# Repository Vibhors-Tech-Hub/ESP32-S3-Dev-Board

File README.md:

# ESP32-S3 Development Board

A professional-grade, high-performance **ESP32-S3 Development Board**. This hardware implementation uses a 4-layer PCB stackup to optimize signal integrity, accommodate controlled-impedance differential USB paths, and provide a low-noise ground reference for the RF module's wireless performance. I needed the ESP32-S3 for many projects, and it's dev kits were out of stock or too expensive locally. So, I challenged myself to build a Dev Board for it myself, and in the same formfactor as that of Espressif, without compromising on signal integrity or double side component placement. 

## Features
* **Core Processor:** ESP32-S3-MINI-1
* **Dual USB Type-C Connectivity:** 
  * **USB OTG Port:** Direct native connection to the ESP32-S3 USB pins (IO19/IO20) for USB Host/Device applications.
  * **USB to UART Port:** Uses a CP2102N in order to get a secondary USB port.
* **Automated Boot Circuit:** Dual NPN transistor (L8050QLT1G) circuit for hands-free flashing and reset toggling via DTR/RTS signals.
* **Power & Protection:** 
  * Linear LDO regulation (**LD1117S33TR**) providing up to 800mA on the 3.3V rail.
  * Input overcurrent protection via a resettable PPTC Polyfuse.
  * Transient Voltage Suppression (TVS) arrays on all VBUS, CC, and USB Data lines to prevent ESD damage.
* **Peripherals & Debugging:**
  * One addressable **SK6812MINI RGB LED** on GPIO 48 for multi-color status indication.
  * User-accessible Boot (IO0) and Reset tactile pushbuttons.
  * Dedicated test points for high-level JTAG debugging (TMS, TCK, TDO, TDI).
  * Two 23-pin expansion headers exposing extensive GPIO arrays, power rails, and ground pins.

## Stackup Configuration
This project utilizes a standard **4-layer stackup** designed to minimize electromagnetic interference (EMI) and provide solid reference planes for the high-frequency RF layout.

*Traces assigned to `USB_OTG` and `USB_UART` lines are routed as **90Ω differential pairs**.

## Hardware Component Configuration

### Power System
* **Input Options:** Powered via the Native USB-C port, UART USB-C port, or the external expansion headers (+5V).
* **Indicator:** An on-board yellow-green LED (`3216SYGC`) provides immediate visual confirmation of a stable 3.3V power rail.

## Manufacturing & Assembly Notes (for maintained differential pair impedance)
* **PCB Thickness:** 1.6 mm
* **Material:** FR-4 (High TG150+ recommended due to the RF component thermal profile)

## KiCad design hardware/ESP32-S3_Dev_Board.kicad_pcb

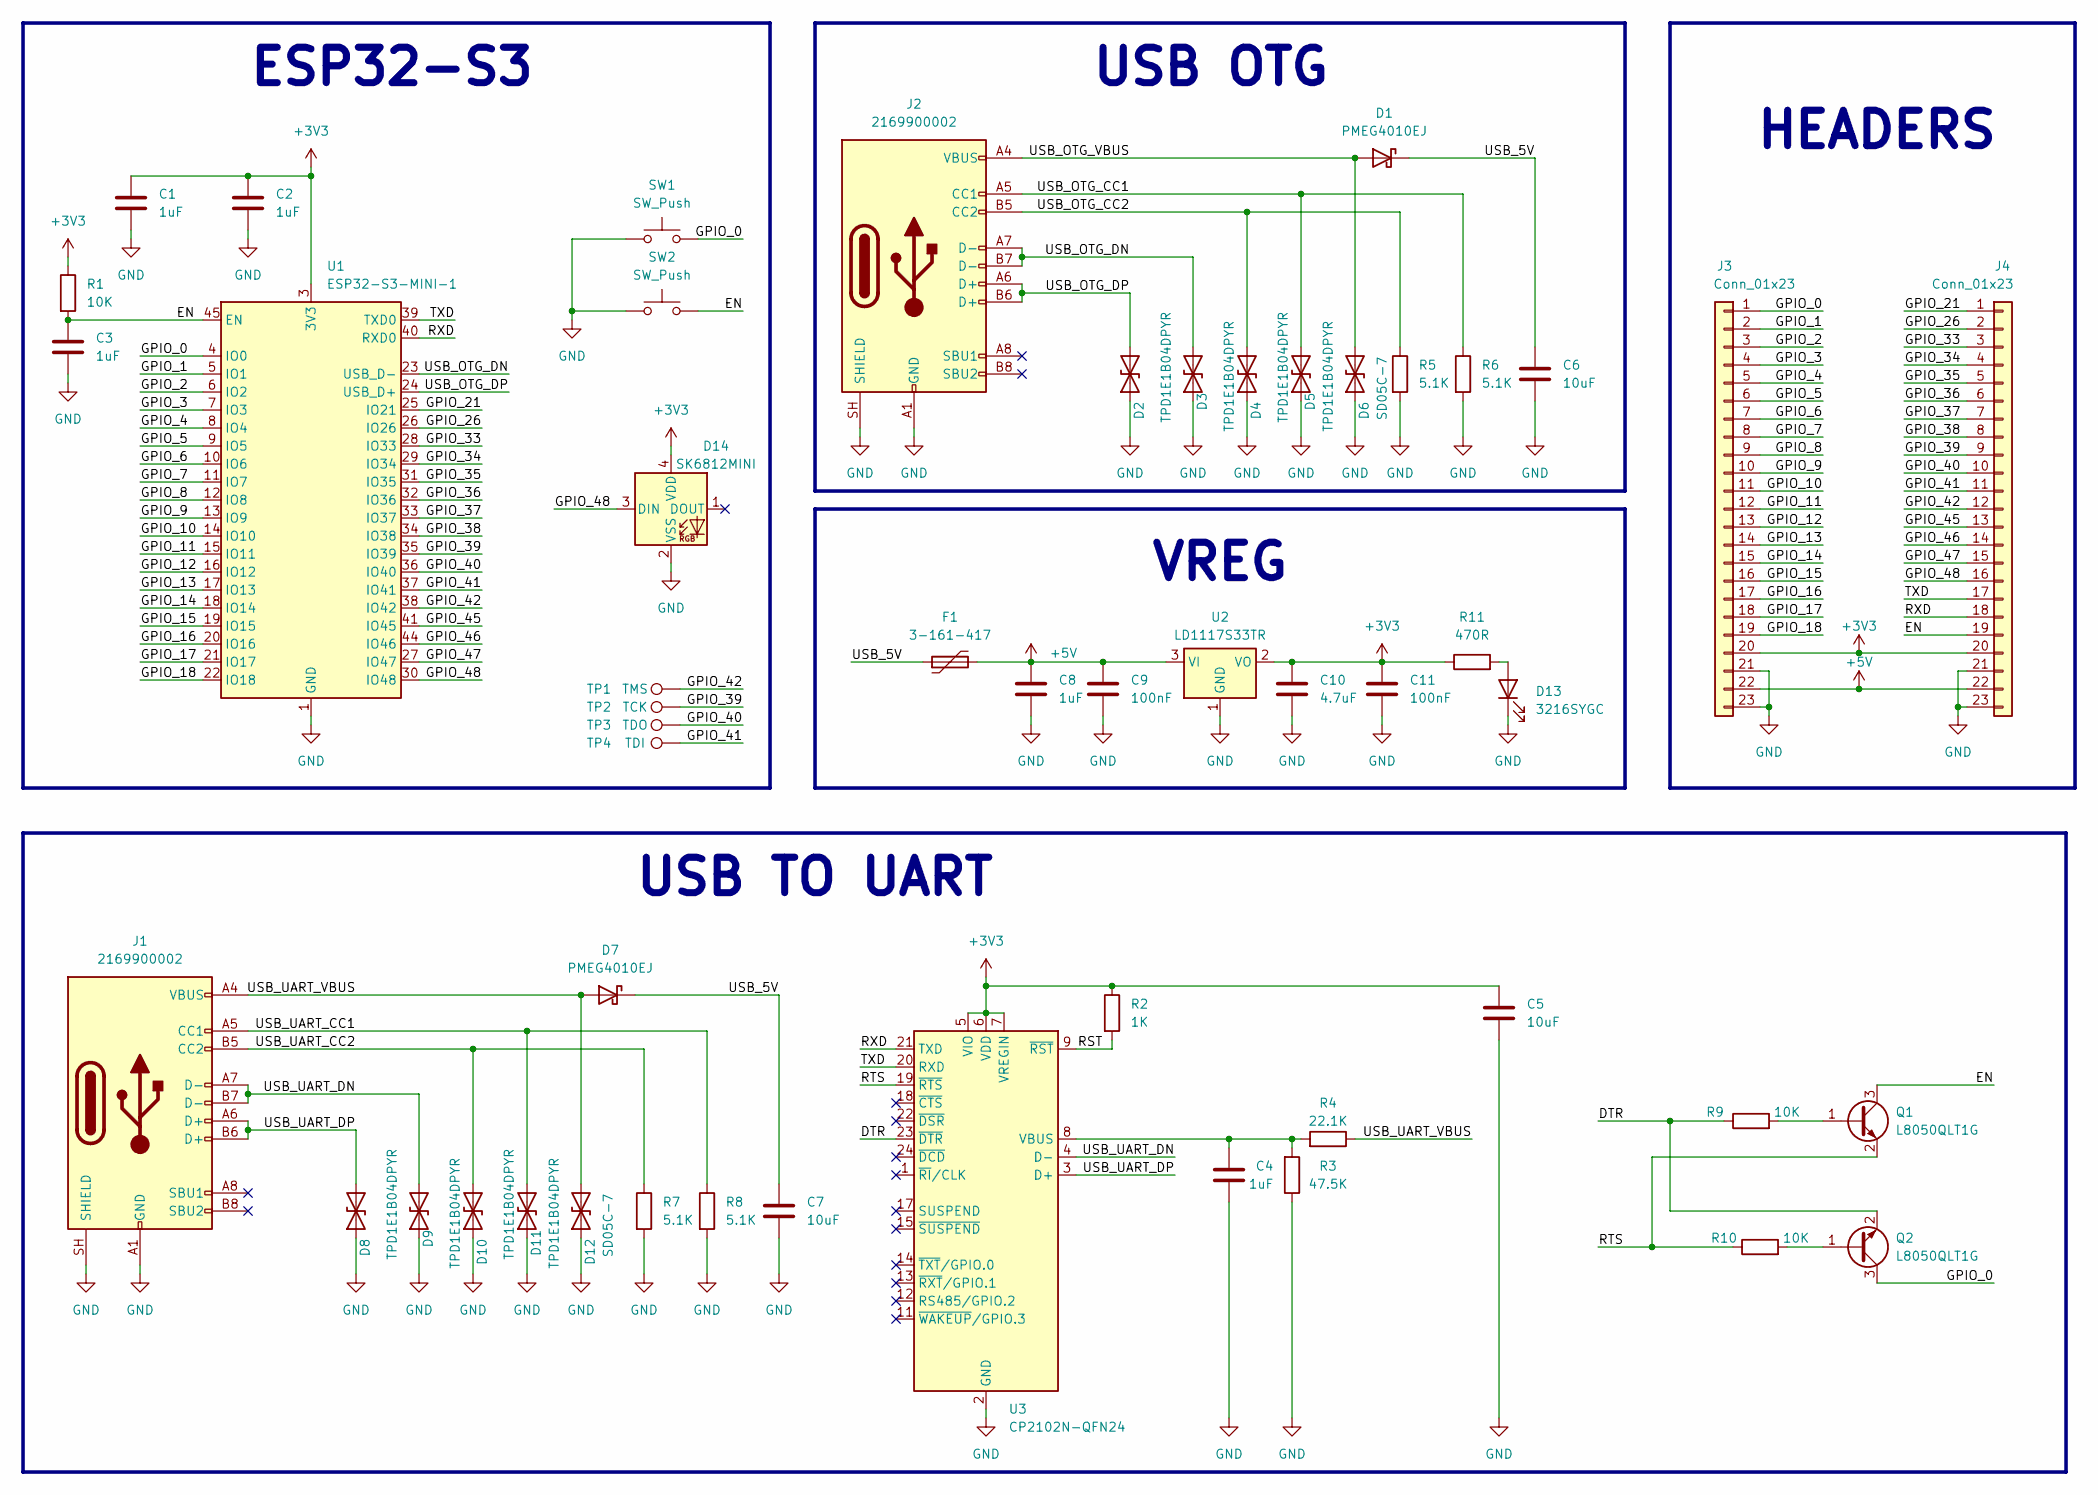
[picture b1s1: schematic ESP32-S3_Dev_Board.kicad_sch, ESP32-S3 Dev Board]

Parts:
C1, C2, C3, C4, C8: 1uF; C_0402_1005Metric_Pad0.74x0.62mm_HandSolder
C5, C6, C7: 10uF; C_0402_1005Metric_Pad0.74x0.62mm_HandSolder
C9, C11: 100nF; C_0402_1005Metric_Pad0.74x0.62mm_HandSolder
C10: 4.7uF; C_0402_1005Metric_Pad0.74x0.62mm_HandSolder
D1, D7: PMEG4010EJ; D_SOD-323F
D2, D3, D4, D5, D8, D9, D10, D11: TPD1E1B04DPYR; D_0402_1005Metric_Pad0.77x0.64mm_HandSolder
D6, D12: SD05C-7; D_0402_1005Metric_Pad0.77x0.64mm_HandSolder
D13: 3216SYGC; LED_1206_3216Metric_Pad1.42x1.75mm_HandSolder
D14: SK6812MINI; LED_SK6812MINI_PLCC4_3.5x3.5mm_P1.75mm
F1: 3-161-417; Fuse_1210_3225Metric_Pad1.42x2.65mm_HandSolder
J1, J2: 2169900002; USB_C_Receptacle_HCTL_HC-TYPE-C-16P-01A
J3, J4: Conn_01x23; PinSocket_1x23_P2.54mm_Vertical
Q1, Q2: L8050QLT1G; SOT-223-3_TabPin2
R1, R9, R10: 10K; R_0402_1005Metric_Pad0.72x0.64mm_HandSolder
R2: 1K; R_0402_1005Metric_Pad0.72x0.64mm_HandSolder
R3: 47.5K; R_0402_1005Metric_Pad0.72x0.64mm_HandSolder
R4: 22.1K; R_0402_1005Metric_Pad0.72x0.64mm_HandSolder
R5, R6, R7, R8: 5.1K; R_0402_1005Metric_Pad0.72x0.64mm_HandSolder
R11: 470R; R_0402_1005Metric_Pad0.72x0.64mm_HandSolder
SW1, SW2: SW_Push; SW_Push_1P1T_NO_Vertical_Wuerth_434133025816
TP1: TMS; TestPoint_Pad_D1.0mm
TP2: TCK; TestPoint_Pad_D1.0mm
TP3: TDO; TestPoint_Pad_D1.0mm
TP4: TDI; TestPoint_Pad_D1.0mm
U1: ESP32-S3-MINI-1; ESP32-S2-MINI-1
U2: LD1117S33TR; SOT-223-3_TabPin2
U3: CP2102N-QFN24; QFN-24-1EP_4x4mm_P0.5mm_EP2.6x2.6mm

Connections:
+3V3: C1.1, C2.1, C5.1, C10.1, C11.1, D14.4 (VDD), J3.20, J4.20, R1.1, R2.1, R11.1, U1.3 (3V3), U2.2 (VO), U3.5 (VIO), U3.6 (VDD), U3.7 (VREGIN)
+5V: C8.1, C9.1, F1.2, J3.22, J4.22, U2.3 (VI)
/DTR: Q2.2 (Emitter), R9.1, U3.23 (~DTR)
/EN: C3.1, J4.19, Q1.3 (Collector), R1.2, SW2.2, U1.45 (EN)
/GPIO_0: J3.1, Q2.3 (Collector), SW1.2, U1.4 (IO0)
/GPIO_1: J3.2, U1.5 (IO1)
/GPIO_2: J3.3, U1.6 (IO2)
/GPIO_3: J3.4, U1.7 (IO3)
/GPIO_4: J3.5, U1.8 (IO4)
/GPIO_5: J3.6, U1.9 (IO5)
/GPIO_6: J3.7, U1.10 (IO6)
/GPIO_7: J3.8, U1.11 (IO7)
/GPIO_8: J3.9, U1.12 (IO8)
/GPIO_9: J3.10, U1.13 (IO9)
/GPIO_10: J3.11, U1.14 (IO10)
/GPIO_11: J3.12, U1.15 (IO11)
/GPIO_12: J3.13, U1.16 (IO12)
/GPIO_13: J3.14, U1.17 (IO13)
/GPIO_14: J3.15, U1.18 (IO14)
/GPIO_15: J3.16, U1.19 (IO15)
/GPIO_16: J3.17, U1.20 (IO16)
/GPIO_17: J3.18, U1.21 (IO17)
/GPIO_18: J3.19, U1.22 (IO18)
/GPIO_21: J4.1, U1.25 (IO21)
/GPIO_26: J4.2, U1.26 (IO26)
/GPIO_33: J4.3, U1.28 (IO33)
/GPIO_34: J4.4, U1.29 (IO34)
/GPIO_35: J4.5, U1.31 (IO35)
/GPIO_36: J4.6, U1.32 (IO36)
/GPIO_37: J4.7, U1.33 (IO37)
/GPIO_38: J4.8, U1.34 (IO38)
/GPIO_39: J4.9, TP2.1 (1_1), U1.35 (IO39)
/GPIO_40: J4.10, TP3.1 (1_1), U1.36 (IO40)
/GPIO_41: J4.11, TP4.1 (1_1), U1.37 (IO41)
/GPIO_42: J4.12, TP1.1 (1_1), U1.38 (IO42)
/GPIO_45: J4.13, U1.41 (IO45)
/GPIO_46: J4.14, U1.44 (IO46)
/GPIO_47: J4.15, U1.27 (IO47)
/GPIO_48: D14.3 (DIN), J4.16, U1.30 (IO48)
/RST: R2.2, U3.9 (~RST)
/RTS: Q1.2 (Emitter), R10.1, U3.19 (~RTS)
/RXD: J4.18, U1.40 (RXD0), U3.21 (TXD)
/TXD: J4.17, U1.39 (TXD0), U3.20 (RXD)
/USB_5V: C6.1, C7.1, D1.1 (K), D7.1 (K), F1.1
/USB_OTG_CC1: D5.2 (A2), J2.A5 (CC1), R6.1
/USB_OTG_CC2: D4.2 (A2), J2.B5 (CC2), R5.1
/USB_OTG_DN: D3.2 (A2), J2.A7 (D-), J2.B7 (D-), U1.23 (USB_D-)
/USB_OTG_DP: D2.2 (A2), J2.A6 (D+), J2.B6 (D+), U1.24 (USB_D+)
/USB_OTG_VBUS: D1.2 (A), D6.2 (A2), J2.A4 (VBUS), J2.A9 (VBUS), J2.B4 (VBUS), J2.B9 (VBUS)
/USB_UART_CC1: D11.2 (A2), J1.A5 (CC1), R8.1
/USB_UART_CC2: D10.2 (A2), J1.B5 (CC2), R7.1
/USB_UART_DN: D9.2 (A2), J1.A7 (D-), J1.B7 (D-), U3.4 (D-)
/USB_UART_DP: D8.2 (A2), J1.A6 (D+), J1.B6 (D+), U3.3 (D+)
/USB_UART_VBUS: D7.2 (A), D12.2 (A2), J1.A4 (VBUS), J1.A9 (VBUS), J1.B4 (VBUS), J1.B9 (VBUS), R4.1
GND: C1.2, C2.2, C3.2, C4.2, C5.2, C6.2, C7.2, C8.2, C9.2, C10.2, C11.2, D2.1 (A1), D3.1 (A1), D4.1 (A1), D5.1 (A1), D6.1 (A1), D8.1 (A1), D9.1 (A1), D10.1 (A1), D11.1 (A1), D12.1 (A1), D13.1 (K), D14.2 (VSS), J1.A1 (GND), J1.A12 (GND), J1.B1 (GND), J1.B12 (GND), J1.SH (SHIELD), J2.A1 (GND), J2.A12 (GND), J2.B1 (GND), J2.B12 (GND), J2.SH (SHIELD), J3.21, J3.23, J4.21, J4.23, R3.1, R5.2, R6.2, R7.2, R8.2, SW1.1, SW2.1, U1.1 (GND), U1.2 (GND), U1.42 (GND), U1.43 (GND), U1.46 (GND), U1.47 (GND), U1.48 (GND), U1.49 (GND), U1.50 (GND), U1.51 (GND), U1.52 (GND), U1.53 (GND), U1.54 (GND), U1.55 (GND), U1.56 (GND), U1.57 (GND), U1.58 (GND), U1.59 (GND), U1.60 (GND), U1.61 (GND), U1.62 (GND), U1.63 (GND), U1.64 (GND), U1.65 (GND), U2.1 (GND), U3.2 (GND), U3.25 (GND)
unnamed: D13.2 (A), R11.2
unnamed: Q1.1 (Base), R9.2
unnamed: Q2.1 (Base), R10.2
unnamed: C4.1, R3.2, R4.2, U3.8 (VBUS)

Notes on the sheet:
ESP32-S3
USB OTG
USB TO UART
VREG
HEADERS

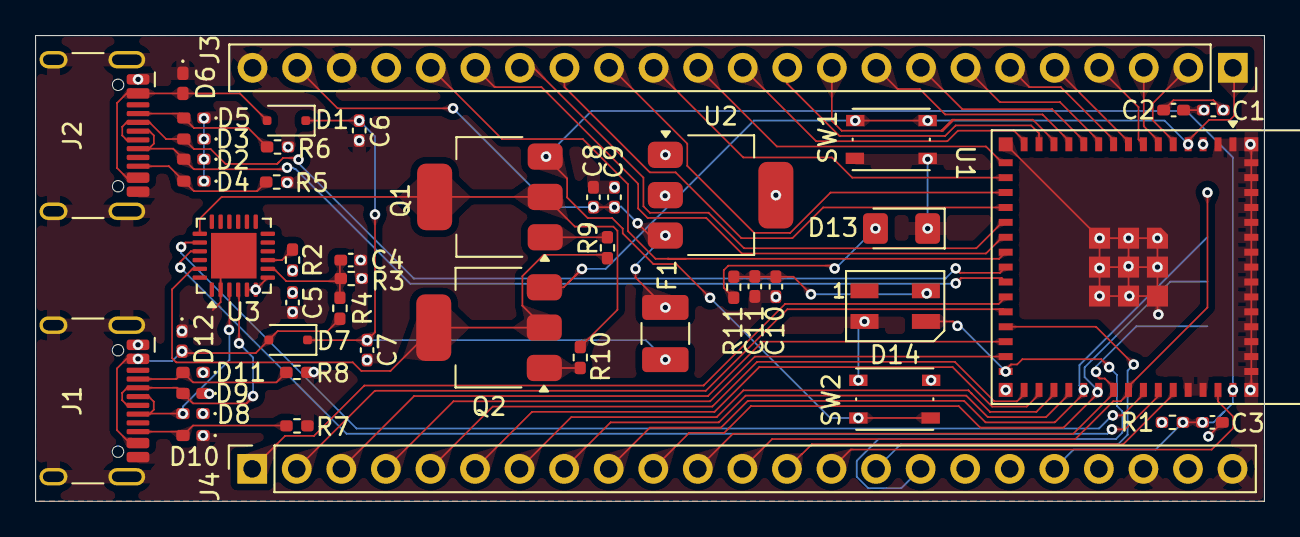
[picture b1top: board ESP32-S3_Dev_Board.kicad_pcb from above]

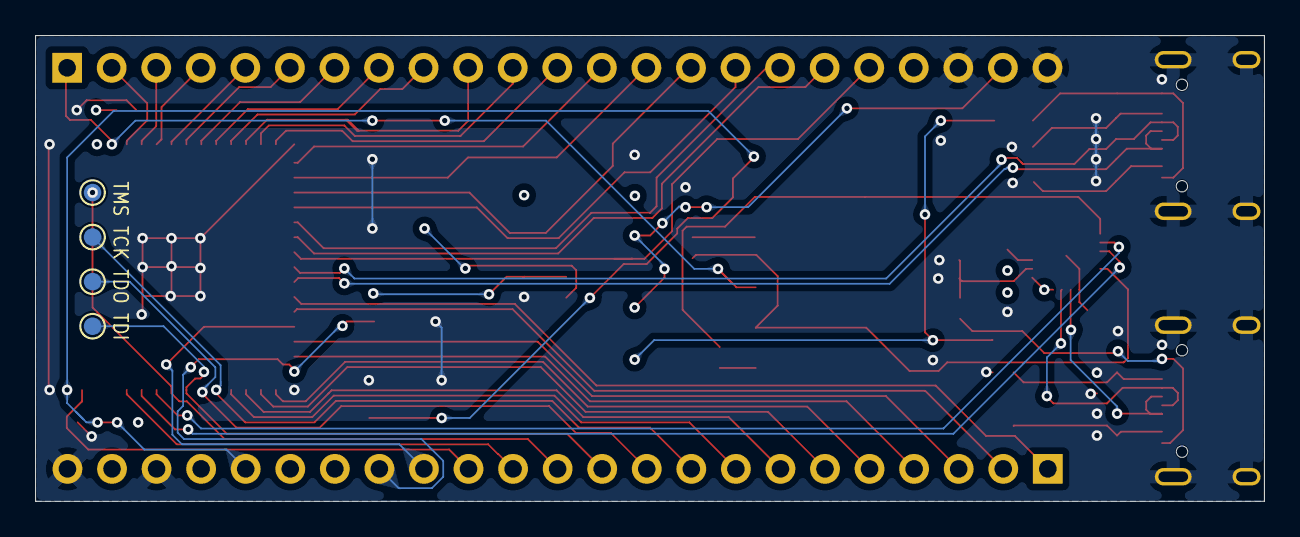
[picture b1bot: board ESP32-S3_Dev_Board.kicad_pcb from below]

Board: 4 copper layers, 70.0 x 26.5 mm, 52 parts (4 on the bottom side), 59 nets.

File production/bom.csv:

"Reference","Qty","Value","DNP","Exclude from BOM","Exclude from Board","Exclude from Simulation","Exclude from Position Files","Footprint","Datasheet"
"C1,C2,C3,C4,C8","5","1uF","","","","","${EXCLUDE_FROM_POS_FILES}","Capacitor_SMD:C_0402_1005Metric_Pad0.74x0.62mm_HandSolder",""
"C5,C6,C7","3","10uF","","","","","${EXCLUDE_FROM_POS_FILES}","Capacitor_SMD:C_0402_1005Metric_Pad0.74x0.62mm_HandSolder",""
"C9,C11","2","100nF","","","","","${EXCLUDE_FROM_POS_FILES}","Capacitor_SMD:C_0402_1005Metric_Pad0.74x0.62mm_HandSolder",""
"C10","1","4.7uF","","","","","${EXCLUDE_FROM_POS_FILES}","Capacitor_SMD:C_0402_1005Metric_Pad0.74x0.62mm_HandSolder",""
"D1,D7","2","PMEG4010EJ","","","","","${EXCLUDE_FROM_POS_FILES}","Diode_SMD:D_SOD-323F","https://datasheet.lcsc.com/lcsc/2204281430_Guangdong-Hottech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"
"D2,D3,D4,D5,D8,D9,D10,D11","8","TPD1E1B04DPYR","","","","","${EXCLUDE_FROM_POS_FILES}","Diode_SMD:D_0402_1005Metric_Pad0.77x0.64mm_HandSolder",""
"D6,D12","2","SD05C-7","","","","","${EXCLUDE_FROM_POS_FILES}","Diode_SMD:D_0402_1005Metric_Pad0.77x0.64mm_HandSolder",""
"D13","1","3216SYGC","","","","","${EXCLUDE_FROM_POS_FILES}","LED_SMD:LED_1206_3216Metric_Pad1.42x1.75mm_HandSolder",""
"D14","1","SK6812MINI","","","","","${EXCLUDE_FROM_POS_FILES}","LED_SMD:LED_SK6812MINI_PLCC4_3.5x3.5mm_P1.75mm","https://cdn-shop.adafruit.com/product-files/2686/SK6812MINI_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"
"F1","1","3-161-417","","","","","${EXCLUDE_FROM_POS_FILES}","Fuse:Fuse_1210_3225Metric_Pad1.42x2.65mm_HandSolder",""
"J1,J2","2","2169900002","","","","","${EXCLUDE_FROM_POS_FILES}","Connector_USB:USB_C_Receptacle_HCTL_HC-TYPE-C-16P-01A","https://www.usb.org/sites/default/files/documents/usb_type-c.zip"
"J3,J4","2","Conn_01x23","","","","","${EXCLUDE_FROM_POS_FILES}","Connector_PinSocket_2.54mm:PinSocket_1x23_P2.54mm_Vertical",""
"Q1,Q2","2","L8050QLT1G","","","","","${EXCLUDE_FROM_POS_FILES}","Package_TO_SOT_SMD:SOT-223-3_TabPin2",""
"R1,R9,R10","3","10K","","","","","${EXCLUDE_FROM_POS_FILES}","Resistor_SMD:R_0402_1005Metric_Pad0.72x0.64mm_HandSolder",""
"R2","1","1K","","","","","${EXCLUDE_FROM_POS_FILES}","Resistor_SMD:R_0402_1005Metric_Pad0.72x0.64mm_HandSolder",""
"R3","1","47.5K","","","","","${EXCLUDE_FROM_POS_FILES}","Resistor_SMD:R_0402_1005Metric_Pad0.72x0.64mm_HandSolder",""
"R4","1","22.1K","","","","","${EXCLUDE_FROM_POS_FILES}","Resistor_SMD:R_0402_1005Metric_Pad0.72x0.64mm_HandSolder",""
"R5,R6,R7,R8","4","5.1K","","","","","${EXCLUDE_FROM_POS_FILES}","Resistor_SMD:R_0402_1005Metric_Pad0.72x0.64mm_HandSolder",""
"R11","1","470R","","","","","${EXCLUDE_FROM_POS_FILES}","Resistor_SMD:R_0402_1005Metric_Pad0.72x0.64mm_HandSolder",""
"SW1,SW2","2","SW_Push","","","","","${EXCLUDE_FROM_POS_FILES}","Button_Switch_SMD:SW_Push_1P1T_NO_Vertical_Wuerth_434133025816",""
"TP1","1","TMS","","","","","${EXCLUDE_FROM_POS_FILES}","TestPoint:TestPoint_Pad_D1.0mm",""
"TP2","1","TCK","","","","","${EXCLUDE_FROM_POS_FILES}","TestPoint:TestPoint_Pad_D1.0mm",""
"TP3","1","TDO","","","","","${EXCLUDE_FROM_POS_FILES}","TestPoint:TestPoint_Pad_D1.0mm",""
"TP4","1","TDI","","","","","${EXCLUDE_FROM_POS_FILES}","TestPoint:TestPoint_Pad_D1.0mm",""
"U1","1","ESP32-S3-MINI-1","","","","","${EXCLUDE_FROM_POS_FILES}","RF_Module:ESP32-S2-MINI-1","https://www.espressif.com/sites/default/files/documentation/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"
"U2","1","LD1117S33TR","","","","","${EXCLUDE_FROM_POS_FILES}","Package_TO_SOT_SMD:SOT-223-3_TabPin2","http://www.st.com/st-web-ui/static/active/en/resource/techni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"
"U3","1","CP2102N-QFN24","","","","","${EXCLUDE_FROM_POS_FILES}","Package_DFN_QFN:QFN-24-1EP_4x4mm_P0.5mm_EP2.6x2.6mm","https://www.silabs.com/documents/public/data-sheets/cp2102n-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"
